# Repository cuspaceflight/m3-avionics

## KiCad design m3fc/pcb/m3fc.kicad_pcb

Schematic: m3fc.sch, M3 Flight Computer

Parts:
C1, C6: 10p; 0402; Farnell 2496790
C2: 4µ7; 0402; Farnell 2426952
C3, C4, C7, C8, C9, C14, C15, C16, C17: 100n; 0402; Farnell 2496771
C5: 1µ; 0402; Farnell 2496814
C10, C11: 2µ2; 0402; Farnell 2362088
C13: 10µ; 0603; Farnell 2456110
D1: RED; 0603-LED; Farnell 2314404
D2: YLW; 0603-LED; Farnell 2335804
D3: GRN; 0603-LED; Farnell 2290363
D4: D; SOD-323; Farnell 1459033
IC1: STM32F405RxTx; LQFP-64; Farnell 2064363
IC2: MS5611-01BA03; MS5611; Farnell 2362662
IC3: MCP2562; DFN-8-EP-MICROCHIP; Farnell 2448755
IC4: ADXL345; ADXL3x5; Farnell 1853935
J1: WEST TOP; TFML-110-02-L-D
J2: WEST BOT; SFML-110-02-L-D-LC
J3: EAST TOP; TFML-110-02-L-D
J4: EAST BOT; SFML-110-02-L-D-LC
LS1: SOUNDER; KSSG13J12-N; Farnell 2215089
P1: SWD_TC; TC2030-NL
Q1: NFET; SOT-23; Farnell 2069541
R1, R2, R3, R4, R5: 100; 0402; Farnell 9239111
Y1: 26M; XTAL-20x16; Farnell 2506952

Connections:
3v3: C2.2, C3.2, C4.2, C5.2, C7.2, C8.2, C9.2, C13.1, C14.1, C16.1, C17.1, D4.1, IC1.1 (VBAT), IC1.13 (VDDA), IC1.19 (VDD), IC1.32 (VDD), IC1.48 (VDD), IC1.64 (VDD), IC2.1 (VDD), IC3.5 (VIO), IC4.1 (VDD_IO), IC4.6 (Vs), J1.7, J2.7, LS1.1, P1.1 (VDD)
/3v3_AUX1: J1.13, J2.13
/3v3_AUX2: J1.15, J2.15
/3v3_DL: J1.11, J2.11
/3v3_IMU: J1.3, J2.3
/3v3_PYRO: J1.9, J2.9
/3v3_RADIO: J1.5, J2.5
/5v_AUX1: J3.11, J4.11
/5v_AUX2: J3.13, J4.13
/5v_CAM: J3.15, J4.15
/5v_CAN: C15.1, IC3.3 (VDD), J1.14, J2.14
/5v_IMU: J3.9, J4.9
/5v_RADIO: J3.7, J4.7
/ACCEL_CS: IC1.45 (PA12), IC4.7 (CS)
/ACCEL_INT: IC1.44 (PA11), IC4.8 (INT1)
/ACCEL_SCLK: IC1.34 (PB13), IC4.14 (SCLK)
/ACCEL_SDI: IC1.36 (PB15), IC4.13 (SDI)
/ACCEL_SDO: IC1.35 (PB14), IC4.12 (SDO)
/BARO_CS: IC1.24 (PC4), IC2.5 (CSB)
/BARO_SCLK: IC1.21 (PA5), IC2.8 (SCLK)
/BARO_SDI: IC1.23 (PA7), IC2.7 (SDI)
/BARO_SDO: IC1.22 (PA6), IC2.6 (SDO)
/BEEPER: IC1.14 (PA0), R1.1
/CAN+: IC3.7 (CANH), J1.18, J2.18
/CAN-: IC3.6 (CANL), J1.16, J2.16
/CAN_RXD: IC1.61 (PB8), IC3.4 (RXD)
/CAN_TXD: IC1.62 (PB9), IC3.1 (TXD)
/CHARGE: J3.17, J3.18, J4.17, J4.18
/JTCK: IC1.49 (PA14), J1.6, J2.6, P1.4 (SWDCLK)
/JTDI: IC1.50 (PA15), J2.8
/JTDO: IC1.55 (PB3), J1.8
/JTDR: J1.10, J2.10
/JTMS: IC1.46 (PA13), J1.4, J2.4, P1.2 (SWDIO)
/LED_GRN: IC1.17 (PA3), R4.1
/LED_RED: IC1.15 (PA1), R2.1
/LED_YLW: IC1.16 (PA2), R3.1
/PWR: J3.16, J4.16
/PYRO1: J3.8, J4.8
/PYRO2: J3.10, J4.10
/PYRO3: J3.12, J4.12
/PYRO4: J3.14, J4.14
/PYRO_SI: J3.5, J3.6, J4.5, J4.6
/PYRO_SO: J3.3, J3.4, J4.3, J4.4
/RSVD1: J1.12, J2.12
/RSVD2: J1.17, J2.17
/~RST: IC1.7 (NRST), P1.3 (~RST)
GND: C1.1, C2.1, C3.1, C4.1, C5.1, C6.2, C7.1, C8.1, C9.1, C10.2, C11.2, C13.2, C14.2, C15.2, C16.2, C17.2, D1.1, D2.1, D3.1, IC1.12 (VSSA), IC1.18 (VSS), IC1.60 (BOOT0), IC1.63 (VSS), IC2.2 (PS), IC2.3 (GND), IC3.2 (VSS), IC3.8 (STBY), IC3.EP (VSS), IC4.2 (GND), IC4.4 (GND), IC4.5 (GND), J1.1, J1.2, J1.19, J1.20, J2.1, J2.2, J2.19, J2.20, J3.1, J3.2, J3.19, J3.20, J4.1, J4.2, J4.19, J4.20, P1.5 (GND), Q1.2 (S), Y1.2, Y1.4
unnamed: C1.2, IC1.5 (PH0), Y1.1
unnamed: C6.1, R5.1, Y1.3
unnamed: C10.1, IC1.47 (VCAP_2)
unnamed: C11.1, IC1.31 (VCAP_1)
unnamed: D1.2, R2.2
unnamed: D2.2, R3.2
unnamed: D3.2, R4.2
unnamed: D4.2, LS1.2, Q1.3 (D)
unnamed: IC1.6 (PH1), R5.2
unnamed: Q1.1 (G), R1.2

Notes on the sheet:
INTERCONNECTS
PB4 is JTRST, DO NOT CONNECT (Errata 2.1.4)

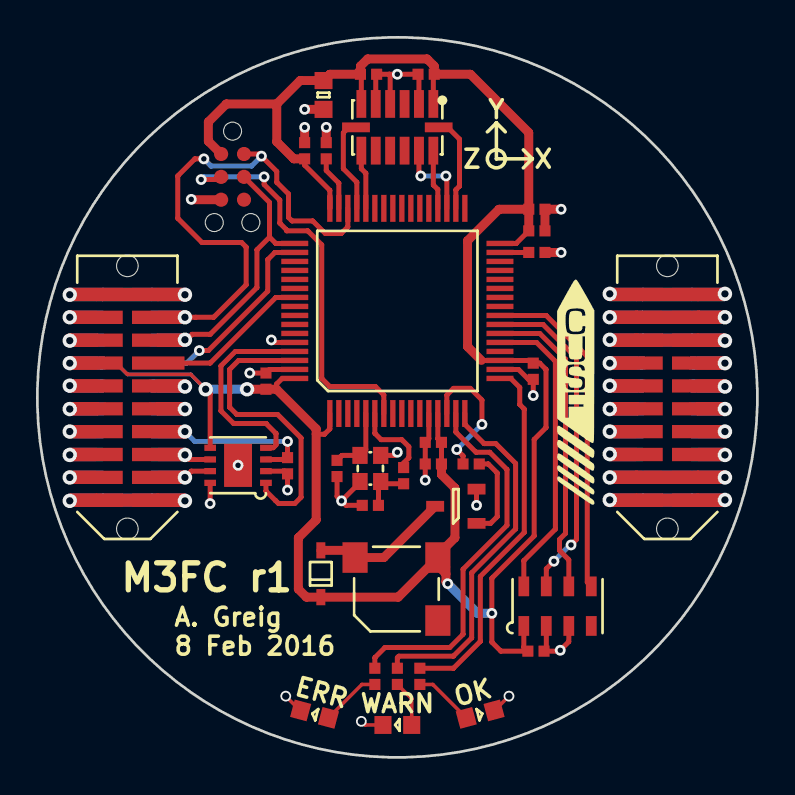
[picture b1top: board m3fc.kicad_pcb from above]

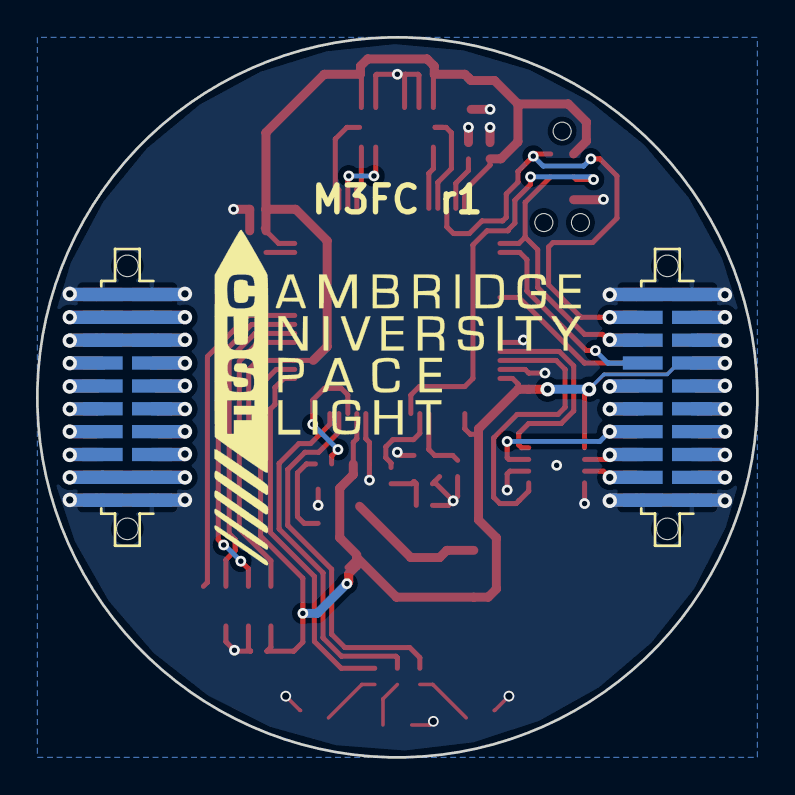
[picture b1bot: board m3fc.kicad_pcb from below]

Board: 2 copper layers, 40.0 x 40.0 mm, 37 parts (2 on the bottom side), 57 nets.

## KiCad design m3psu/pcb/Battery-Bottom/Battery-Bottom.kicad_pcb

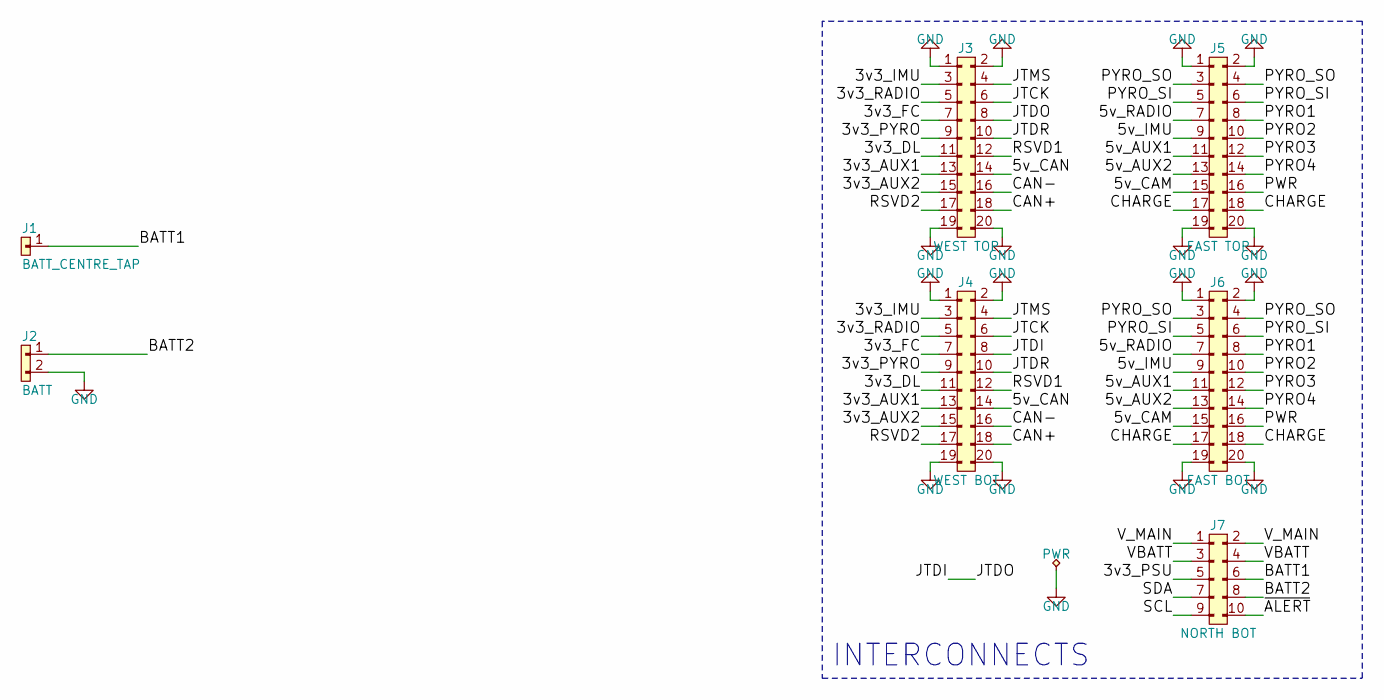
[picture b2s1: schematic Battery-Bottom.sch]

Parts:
J1: BATT_CENTRE_TAP; Socket_Strip_Straight_1x01
J2: BATT; Socket_Strip_Straight_1x02
J3: WEST TOP; TFML-110-02-L-D
J4: WEST BOT; SFML-110-02-L-D-LC
J5: EAST TOP; TFML-110-02-L-D
J6: EAST BOT; SFML-110-02-L-D-LC
J7: NORTH BOT; SFML-105-02-L-D-LC

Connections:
/3v3_AUX1: J3.13, J4.13
/3v3_AUX2: J3.15, J4.15
/3v3_DL: J3.11, J4.11
/3v3_FC: J3.7, J4.7
/3v3_IMU: J3.3, J4.3
/3v3_PSU: J7.5
/3v3_PYRO: J3.9, J4.9
/3v3_RADIO: J3.5, J4.5
/5v_AUX1: J5.11, J6.11
/5v_AUX2: J5.13, J6.13
/5v_CAM: J5.15, J6.15
/5v_CAN: J3.14, J4.14
/5v_IMU: J5.9, J6.9
/5v_RADIO: J5.7, J6.7
/BATT1: J1.1, J7.6
/BATT2: J2.1, J7.8
/CAN+: J3.18, J4.18
/CAN-: J3.16, J4.16
/CHARGE: J5.17, J5.18, J6.17, J6.18
/JTCK: J3.6, J4.6
/JTDI: J3.8, J4.8
/JTDR: J3.10, J4.10
/JTMS: J3.4, J4.4
/PWR: J5.16, J6.16
/PYRO1: J5.8, J6.8
/PYRO2: J5.10, J6.10
/PYRO3: J5.12, J6.12
/PYRO4: J5.14, J6.14
/PYRO_SI: J5.5, J5.6, J6.5, J6.6
/PYRO_SO: J5.3, J5.4, J6.3, J6.4
/RSVD1: J3.12, J4.12
/RSVD2: J3.17, J4.17
/SCL: J7.9
/SDA: J7.7
/VBATT: J7.3, J7.4
/V_MAIN: J7.1, J7.2
/~ALERT: J7.10
GND: J2.2, J3.1, J3.2, J3.19, J3.20, J4.1, J4.2, J4.19, J4.20, J5.1, J5.2, J5.19, J5.20, J6.1, J6.2, J6.19, J6.20

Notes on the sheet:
INTERCONNECTS

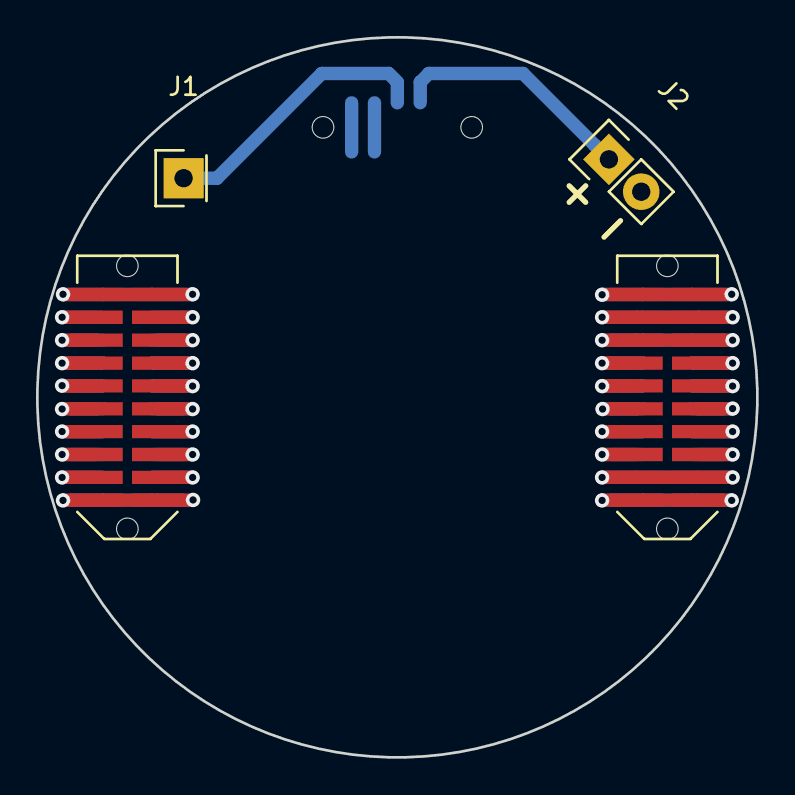
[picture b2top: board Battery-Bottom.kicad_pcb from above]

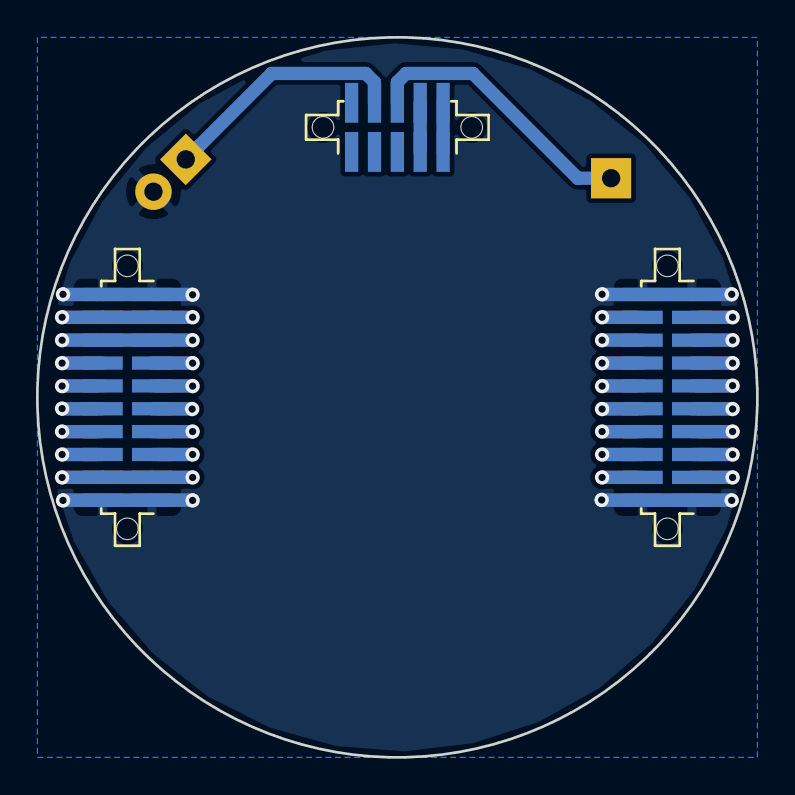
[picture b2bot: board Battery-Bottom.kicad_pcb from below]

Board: 2 copper layers, 40.0 x 40.0 mm, 7 parts (3 on the bottom side), 34 nets.

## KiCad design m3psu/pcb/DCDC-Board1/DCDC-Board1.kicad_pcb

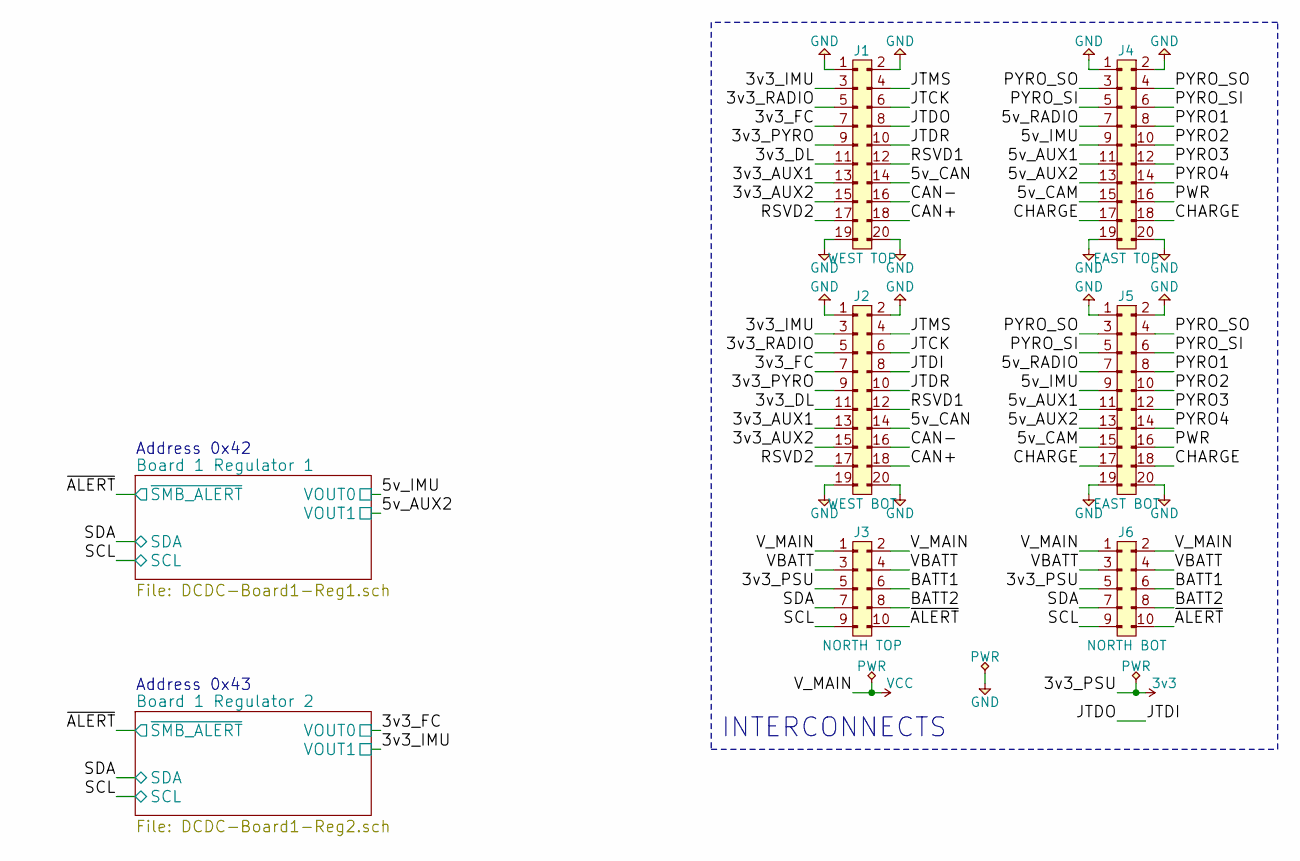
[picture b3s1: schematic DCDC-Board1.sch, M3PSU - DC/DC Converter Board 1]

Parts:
J1: WEST TOP; TFML-110-02-L-D
J2: WEST BOT; SFML-110-02-L-D-LC
J3: NORTH TOP; TFML-105-02-L-D
J4: EAST TOP; TFML-110-02-L-D
J5: EAST BOT; SFML-110-02-L-D-LC
J6: NORTH BOT; SFML-105-02-L-D-LC

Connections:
3v3: J3.5, J6.5
/3v3_AUX1: J1.13, J2.13
/3v3_AUX2: J1.15, J2.15
/3v3_DL: J1.11, J2.11
/3v3_FC: J1.7, J2.7; also elsewhere on the board
/3v3_IMU: J1.3, J2.3; also elsewhere on the board
/3v3_PYRO: J1.9, J2.9
/3v3_RADIO: J1.5, J2.5
/5v_AUX1: J4.11, J5.11
/5v_AUX2: J4.13, J5.13; also elsewhere on the board
/5v_CAM: J4.15, J5.15
/5v_CAN: J1.14, J2.14
/5v_IMU: J4.9, J5.9; also elsewhere on the board
/5v_RADIO: J4.7, J5.7
/BATT1: J3.6, J6.6
/BATT2: J3.8, J6.8
/CAN+: J1.18, J2.18
/CAN-: J1.16, J2.16
/CHARGE: J4.17, J4.18, J5.17, J5.18
/JTCK: J1.6, J2.6
/JTDI: J1.8, J2.8
/JTDR: J1.10, J2.10
/JTMS: J1.4, J2.4
/PWR: J4.16, J5.16
/PYRO1: J4.8, J5.8
/PYRO2: J4.10, J5.10
/PYRO3: J4.12, J5.12
/PYRO4: J4.14, J5.14
/PYRO_SI: J4.5, J4.6, J5.5, J5.6
/PYRO_SO: J4.3, J4.4, J5.3, J5.4
/RSVD1: J1.12, J2.12
/RSVD2: J1.17, J2.17
/SCL: J3.9, J6.9; also elsewhere on the board
/SDA: J3.7, J6.7; also elsewhere on the board
/VBATT: J3.3, J3.4, J6.3, J6.4
/~ALERT: J3.10, J6.10; also elsewhere on the board
GND: J1.1, J1.2, J1.19, J1.20, J2.1, J2.2, J2.19, J2.20, J4.1, J4.2, J4.19, J4.20, J5.1, J5.2, J5.19, J5.20; also elsewhere on the board
VCC: J3.1, J3.2, J6.1, J6.2; also elsewhere on the board

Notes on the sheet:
Address 0x42
Address 0x43
INTERCONNECTS

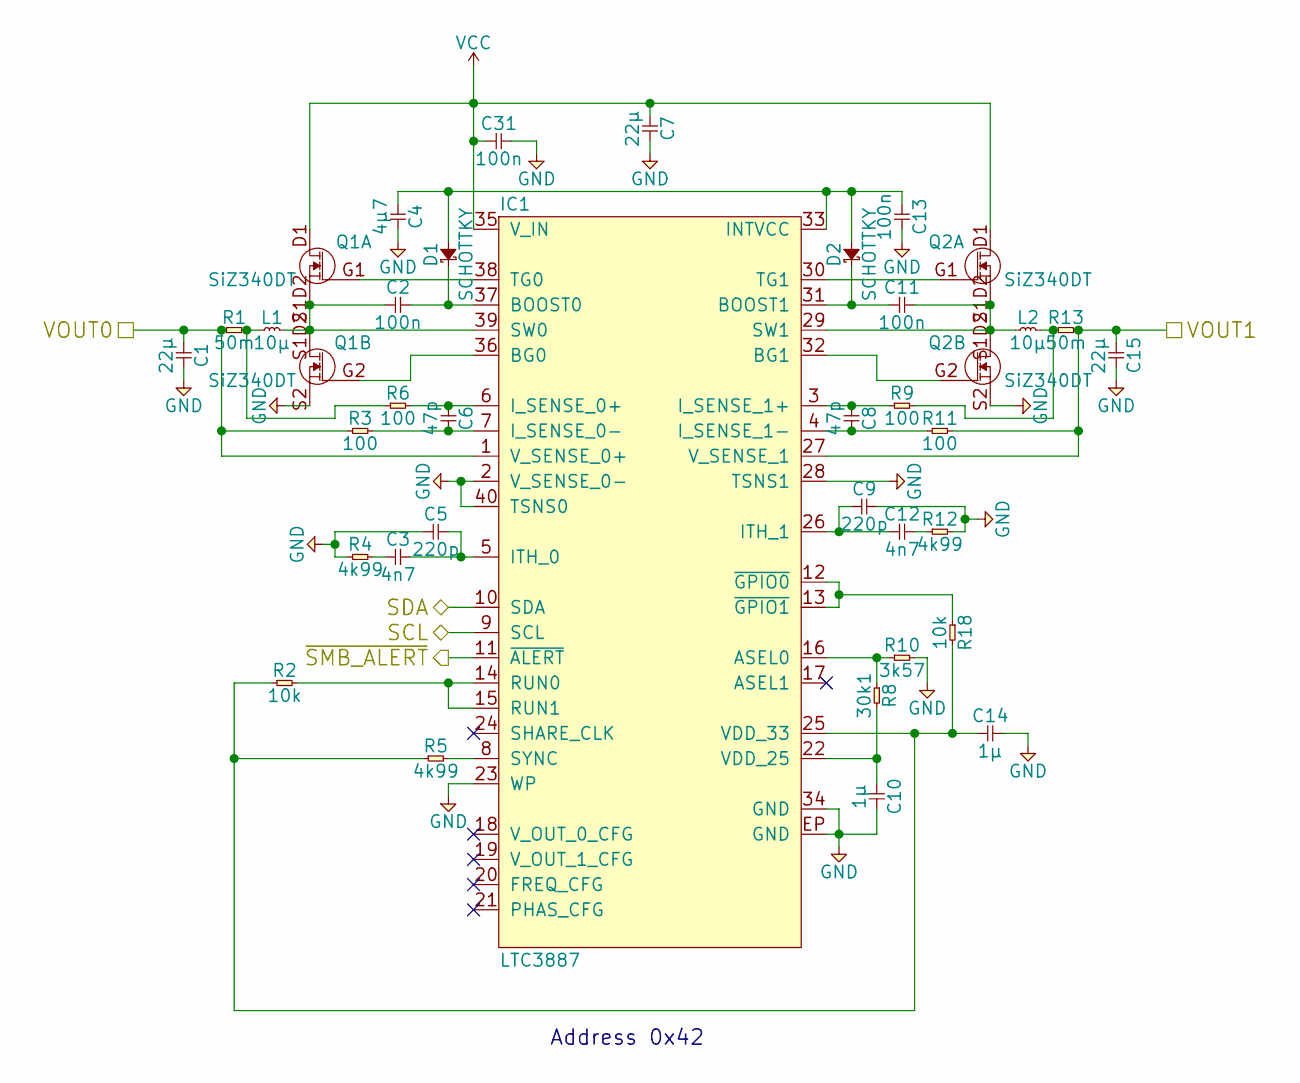
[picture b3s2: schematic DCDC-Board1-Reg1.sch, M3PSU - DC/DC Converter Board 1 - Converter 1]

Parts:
C1, C7, C15: 22µ; 0805; Farnell 2346925
C2, C11, C13, C31: 100n; 0402; Farnell 2496811
C3, C12: 4n7; 0402; Farnell 2496786
C4: 4µ7; 0402; Farnell 2346881
C5, C9: 220p; 0402; Farnell 2210772
C6, C8: 47p; 0402; Farnell 2210781
C10, C14: 1µ; 0402; Farnell 2218855
D1, D2: SCHOTTKY; 0603-LED; Farnell 2317558
IC1: LTC3887; QFN-40-EP-LTC-UJ; Farnell 2475658
L1, L2: 10µ; TYS5040; Farnell 2292532
Q1, Q2: SiZ340DT; PowerPair3x3; Farnell 2422226
R1, R13: 50m; 0603; Farnell 1506129
R2, R18: 10k; 0402; Farnell 2447096
R3, R6, R9, R11: 100; 0402; Farnell 2447095
R4, R5, R12: 4k99; 0402; Farnell 1469715
R8: 30k1; 0402; Farnell 2072900
R10: 3k57; 0402; Farnell 2302693

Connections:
/5v_AUX2: C15.1, IC1.27 (V_SENSE_1), R11.2, R13.2; also elsewhere on the board
/5v_IMU: C1.1, IC1.1 (V_SENSE_0+), R1.1, R3.1; also elsewhere on the board
/SCL: IC1.9 (SCL); also elsewhere on the board
/SDA: IC1.10 (SDA); also elsewhere on the board
/~ALERT: IC1.11 (~ALERT); also elsewhere on the board
GND: C1.2, C4.2, C5.1, C7.2, C9.2, C10.2, C13.2, C14.2, C15.2, C31.2, IC1.2 (V_SENSE_0-), IC1.23 (WP), IC1.28 (TSNS1), IC1.34 (GND), IC1.40 (TSNS0), IC1.EP (GND), Q1.S2, Q2.S2, R4.1, R10.2, R12.2; also elsewhere on the board
unnamed: C2.1, IC1.39 (SW0), L1.2, Q1.S1D2
unnamed: C2.2, D1.1, IC1.37 (BOOST0)
unnamed: C3.1, R4.2
unnamed: C3.2, C5.2, IC1.5 (ITH_0)
unnamed: C6.1, IC1.6 (I_SENSE_0+), R6.2
unnamed: C6.2, IC1.7 (I_SENSE_0-), R3.2
unnamed: C8.1, IC1.3 (I_SENSE_1+), R9.1
unnamed: C8.2, IC1.4 (I_SENSE_1-), R11.1
unnamed: C10.1, IC1.22 (VDD_25), R8.2
unnamed: C11.1, D2.1, IC1.31 (BOOST1)
unnamed: C11.2, IC1.29 (SW1), L2.1, Q2.S1D2
unnamed: C9.1, C12.1, IC1.26 (ITH_1)
unnamed: C12.2, R12.1
unnamed: C4.1, C13.1, D1.2, D2.2, IC1.33 (INTVCC)
unnamed: C14.1, IC1.25 (VDD_33), R2.1, R5.1, R18.2
unnamed: IC1.8 (SYNC), R5.2
unnamed: IC1.12 (~GPIO0), IC1.13 (~GPIO1), R18.1
unnamed: IC1.14 (RUN0), IC1.15 (RUN1), R2.2
unnamed: IC1.16 (ASEL0), R8.1, R10.1
unnamed: IC1.30 (TG1), Q2.G1
unnamed: IC1.32 (BG1), Q2.G2
unnamed: IC1.36 (BG0), Q1.G2
unnamed: IC1.38 (TG0), Q1.G1
unnamed: L1.1, R1.2, R6.1
unnamed: L2.2, R9.2, R13.1
VCC: C7.1, C31.1, IC1.35 (V_IN), Q1.D1 (S1D2), Q2.D1 (S1D2); also elsewhere on the board

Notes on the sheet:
Address 0x42

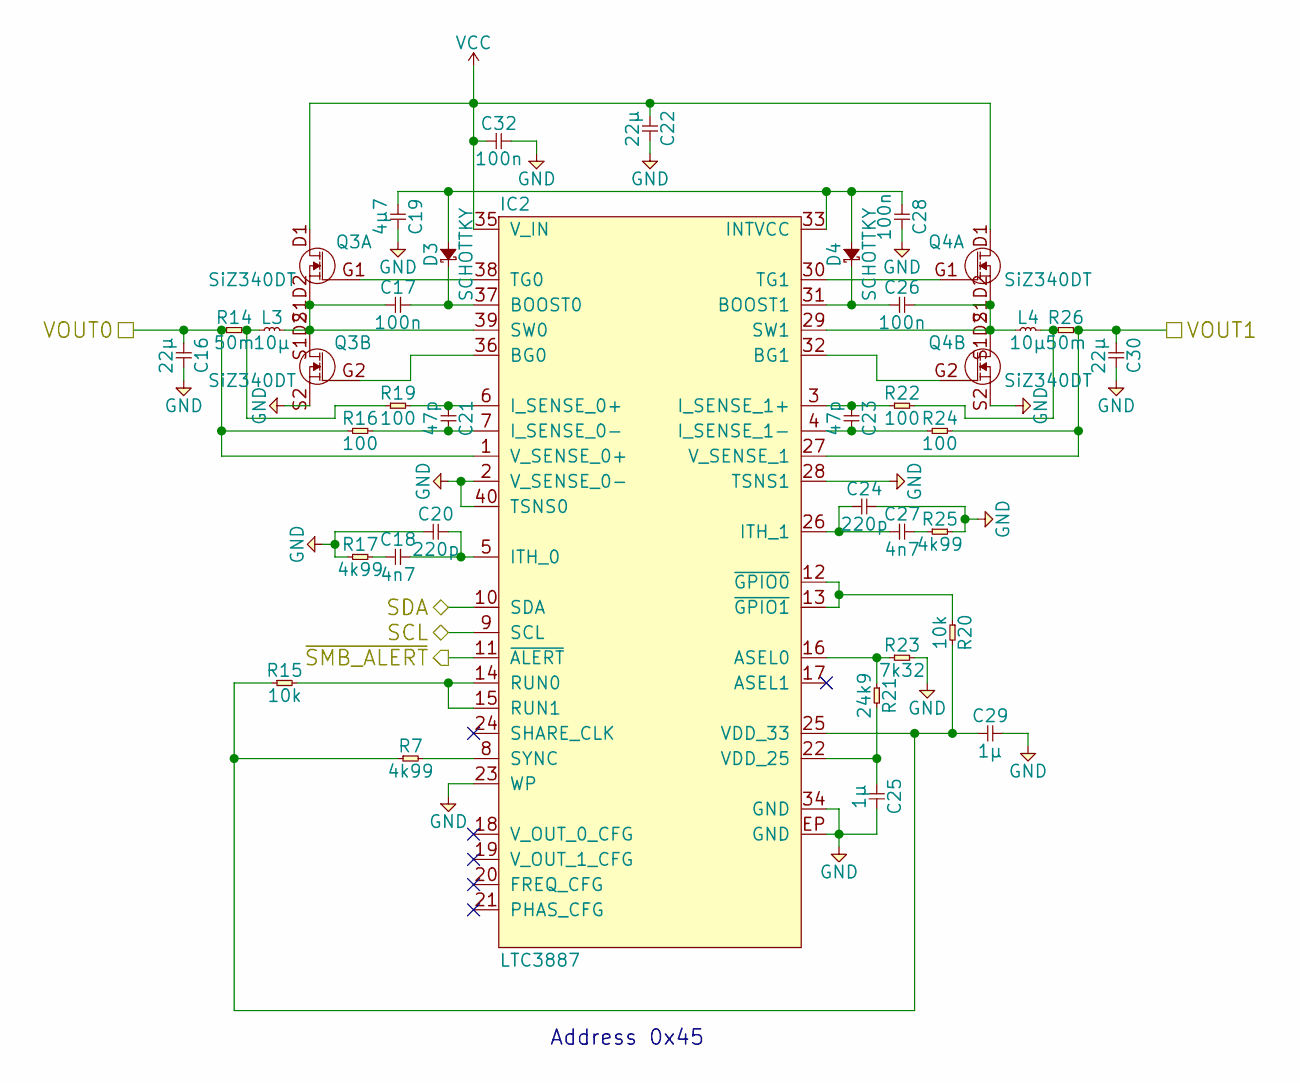
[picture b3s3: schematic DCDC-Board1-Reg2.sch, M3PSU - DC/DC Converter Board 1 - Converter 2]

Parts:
C16, C22, C30: 22µ; 0805; Farnell 2346925
C17, C26, C28, C32: 100n; 0402; Farnell 2496811
C18, C27: 4n7; 0402; Farnell 2496786
C19: 4µ7; 0402; Farnell 2346881
C20, C24: 220p; 0402; Farnell 2210772
C21, C23: 47p; 0402; Farnell 2210781
C25, C29: 1µ; 0402; Farnell 2218855
D3, D4: SCHOTTKY; 0603-LED; Farnell 2317558
IC2: LTC3887; QFN-40-EP-LTC-UJ; Farnell 2475658
L3, L4: 10µ; TYS5040; Farnell 2292532
Q3, Q4: SiZ340DT; PowerPair3x3; Farnell 2422226
R7, R17, R25: 4k99; 0402; Farnell 1469715
R14, R26: 50m; 0603; Farnell 1506129
R15, R20: 10k; 0402; Farnell 2447096
R16, R19, R22, R24: 100; 0402; Farnell 2447095
R21: 24k9; 0402; Farnell 1803690
R23: 7k32; 0402; Farnell 2073037

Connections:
/3v3_FC: C16.1, IC2.1 (V_SENSE_0+), R14.1, R16.1; also elsewhere on the board
/3v3_IMU: C30.1, IC2.27 (V_SENSE_1), R24.2, R26.2; also elsewhere on the board
/SCL: IC2.9 (SCL); also elsewhere on the board
/SDA: IC2.10 (SDA); also elsewhere on the board
/~ALERT: IC2.11 (~ALERT); also elsewhere on the board
GND: C16.2, C19.2, C20.1, C22.2, C24.2, C25.2, C28.2, C29.2, C30.2, C32.2, IC2.2 (V_SENSE_0-), IC2.23 (WP), IC2.28 (TSNS1), IC2.34 (GND), IC2.40 (TSNS0), IC2.EP (GND), Q3.S2, Q4.S2, R17.1, R23.2, R25.2; also elsewhere on the board
unnamed: C17.1, IC2.39 (SW0), L3.2, Q3.S1D2
unnamed: C17.2, D3.1, IC2.37 (BOOST0)
unnamed: C18.1, R17.2
unnamed: C18.2, C20.2, IC2.5 (ITH_0)
unnamed: C19.1, C28.1, D3.2, D4.2, IC2.33 (INTVCC)
unnamed: C21.1, IC2.6 (I_SENSE_0+), R19.2
unnamed: C21.2, IC2.7 (I_SENSE_0-), R16.2
unnamed: C23.1, IC2.3 (I_SENSE_1+), R22.1
unnamed: C23.2, IC2.4 (I_SENSE_1-), R24.1
unnamed: C24.1, C27.1, IC2.26 (ITH_1)
unnamed: C25.1, IC2.22 (VDD_25), R21.2
unnamed: C26.1, D4.1, IC2.31 (BOOST1)
unnamed: C26.2, IC2.29 (SW1), L4.1, Q4.S1D2
unnamed: C27.2, R25.1
unnamed: C29.1, IC2.25 (VDD_33), R7.1, R15.1, R20.2
unnamed: IC2.8 (SYNC), R7.2
unnamed: IC2.12 (~GPIO0), IC2.13 (~GPIO1), R20.1
unnamed: IC2.14 (RUN0), IC2.15 (RUN1), R15.2
unnamed: IC2.16 (ASEL0), R21.1, R23.1
unnamed: IC2.30 (TG1), Q4.G1
unnamed: IC2.32 (BG1), Q4.G2
unnamed: IC2.36 (BG0), Q3.G2
unnamed: IC2.38 (TG0), Q3.G1
unnamed: L3.1, R14.2, R19.1
unnamed: L4.2, R22.2, R26.1
VCC: C22.1, C32.1, IC2.35 (V_IN), Q3.D1 (S1D2), Q4.D1 (S1D2); also elsewhere on the board

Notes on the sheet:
Address 0x45

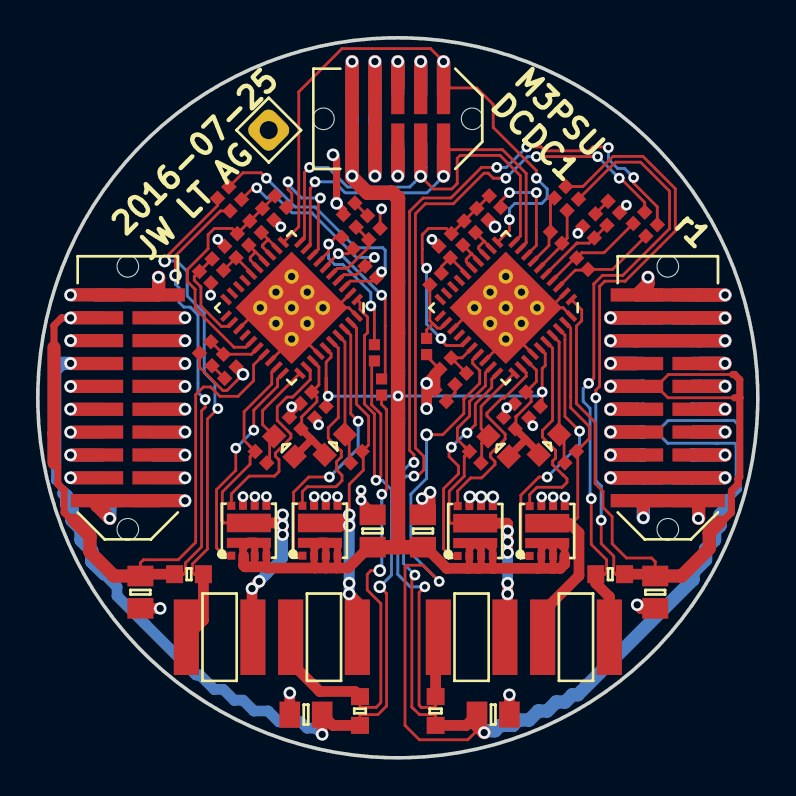
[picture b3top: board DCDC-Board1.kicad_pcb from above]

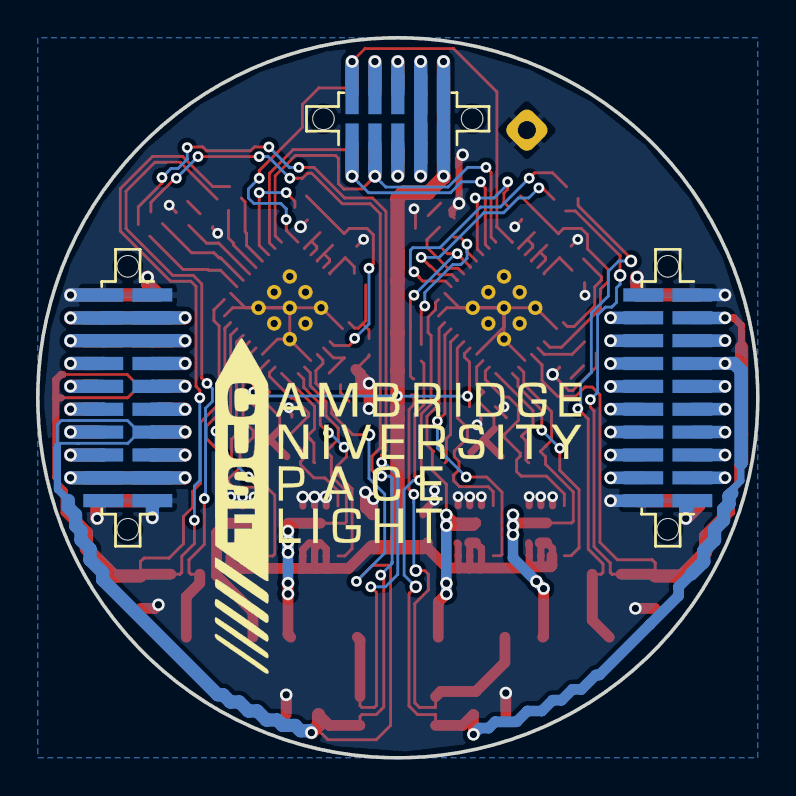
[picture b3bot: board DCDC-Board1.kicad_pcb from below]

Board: 2 copper layers, 40.0 x 40.0 mm, 78 parts (3 on the bottom side), 88 nets.

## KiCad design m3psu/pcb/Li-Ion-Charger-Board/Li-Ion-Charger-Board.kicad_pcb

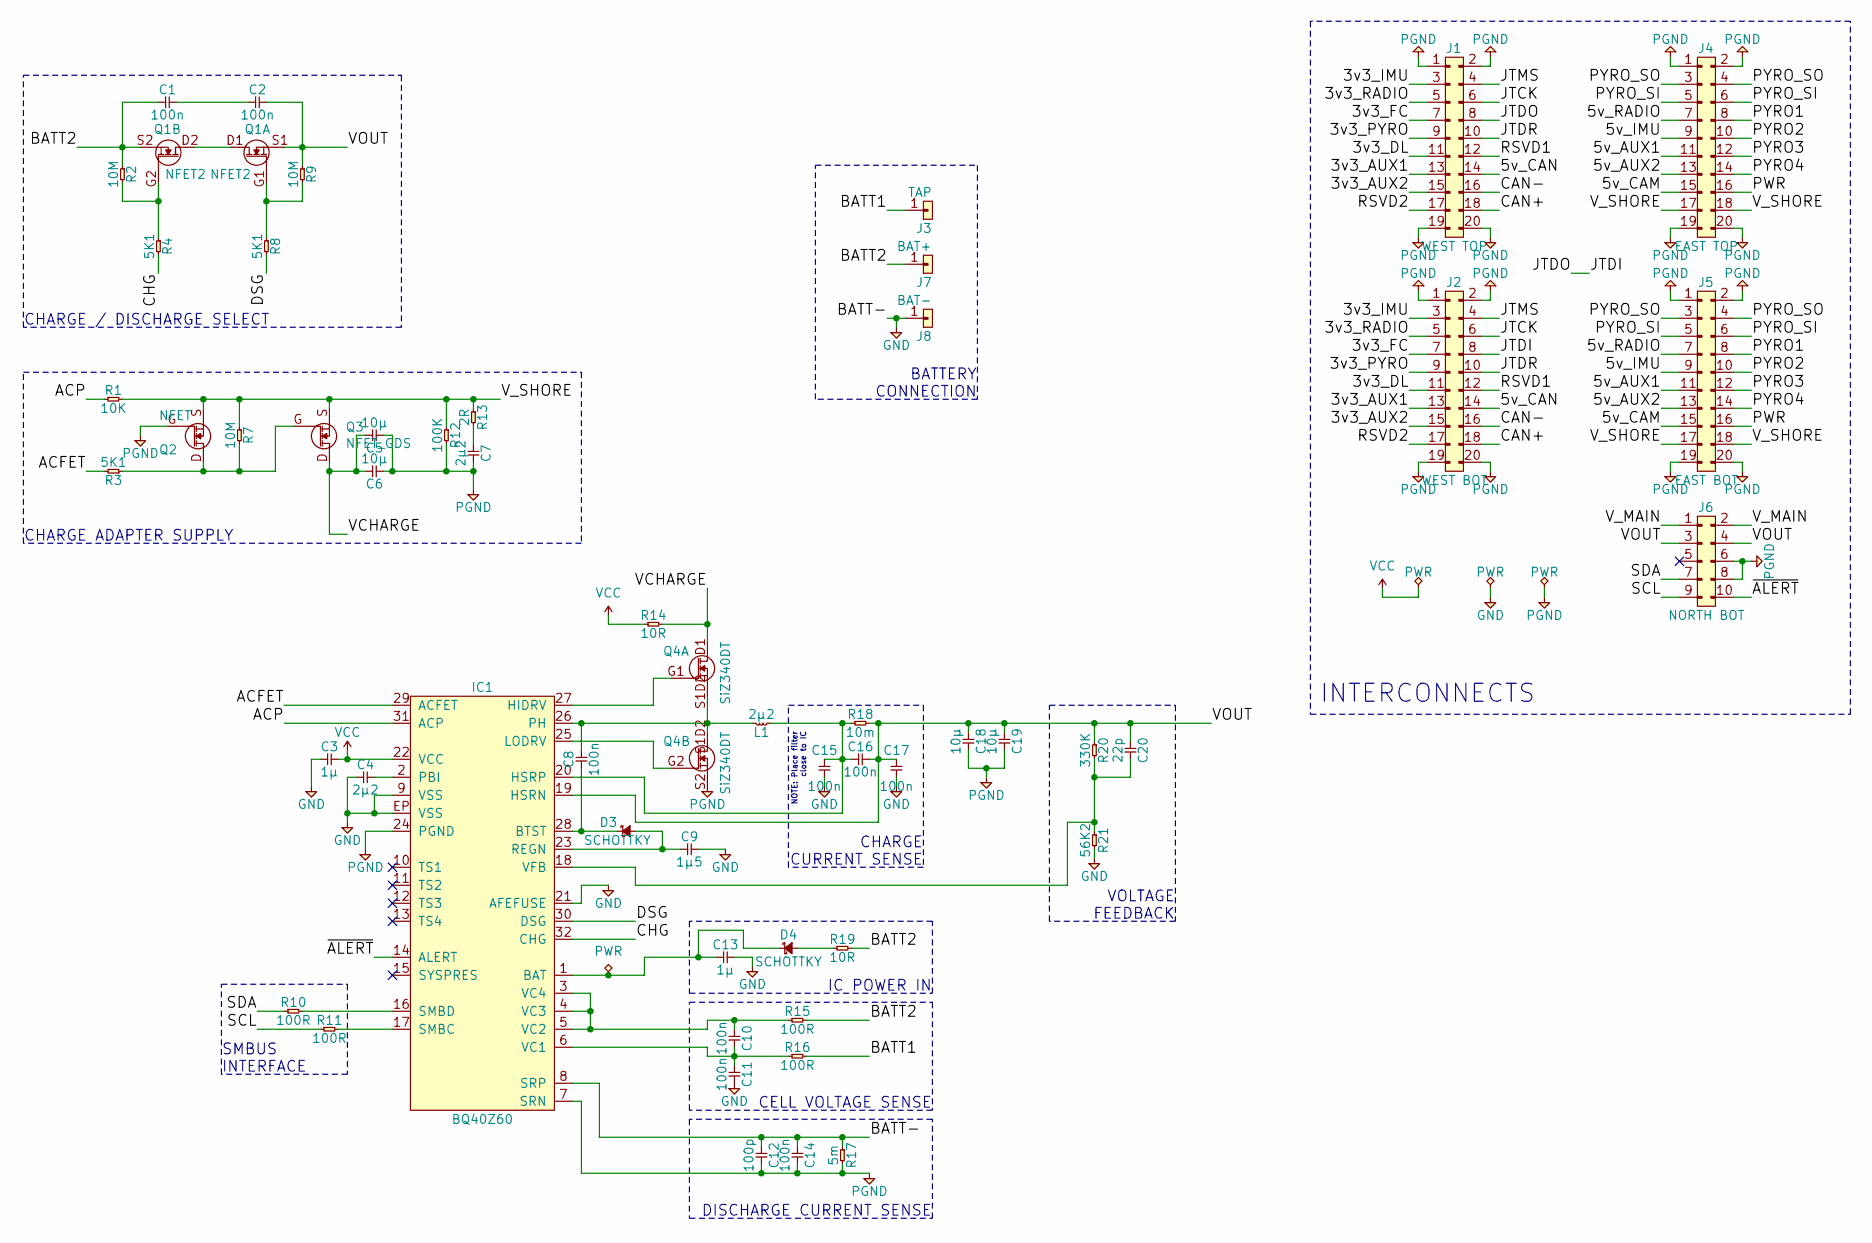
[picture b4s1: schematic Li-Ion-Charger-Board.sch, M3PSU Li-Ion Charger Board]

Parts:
C1, C2, C8, C10, C11, C14, C15, C16, C17: 100n; 0402; Farnell 2218856
C3, C13: 1µ; 0402; Farnell 2218855
C4, C7: 2µ2; 0805; Farnell 1657931
C5, C6, C18, C19: 10µ; 1210; Farnell 1845762
C9: 1µ5; 0603; Farnell 2211176
C12: 100p; 0402; Farnell 2496792
C20: 22p; 0402; Farnell 2496799
D3, D4: SCHOTTKY; SOD-323; Farnell 1459033
IC1: BQ40Z60; QFN-32-EP-TI; Farnell 2471154
J1: WEST TOP; TFML-110-02-L-D
J2: WEST BOT; SFML-110-02-L-D-LC
J3: TAP; SIL-254P-01
J4: EAST TOP; TFML-110-02-L-D
J5: EAST BOT; SFML-110-02-L-D-LC
J6: NORTH BOT; SFML-105-02-L-D-LC
J7: BAT+; SIL-254P-01
J8: BAT-; SIL-254P-01
L1: 2µ2; SRP5030T; Farnell 2309885
Q1: NFET2; PowerFLAT-5x6; Farnell 2098274
Q2: NFET; SOT-883-B; Farnell 2498598
Q3: NFET_GDS; SON2x2N; Farnell 2544998
Q4: SiZ340DT; PowerPair-3x3; Farnell 2422226
R1: 10K; 0402; Farnell 1469669
R2, R7, R9: 10M; 0402; Farnell 1469670
R3, R4, R8: 5K1; 0402; Farnell 1458805
R10, R11, R15, R16: 100R; 0402; Farnell 9239111
R12: 100K; 0402; Farnell 9239472
R13: 2R; 0402; Farnell 2059192
R14, R19: 10R; 0402; Farnell 1652742
R17: 5m; 0805; Farnell 2518218
R18: 10m; 0603; Farnell 2503038
R20: 330K; 0402; Farnell 2502450
R21: 56K2; 0402; Farnell 2059175

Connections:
/3v3_AUX1: J1.13, J2.13
/3v3_AUX2: J1.15, J2.15
/3v3_DL: J1.11, J2.11
/3v3_FC: J1.7, J2.7
/3v3_IMU: J1.3, J2.3
/3v3_PYRO: J1.9, J2.9
/3v3_RADIO: J1.5, J2.5
/5v_AUX1: J4.11, J5.11
/5v_AUX2: J4.13, J5.13
/5v_CAM: J4.15, J5.15
/5v_CAN: J1.14, J2.14
/5v_IMU: J4.9, J5.9
/5v_RADIO: J4.7, J5.7
/ACFET: IC1.29 (ACFET), R3.2
/ACP: IC1.31 (ACP), R1.1
/BATT1: J3.1, R16.2
/BATT2: C1.1, J7.1, Q1.S2 (S), R2.1, R15.2, R19.2
/CAN+: J1.18, J2.18
/CAN-: J1.16, J2.16
/CHG: IC1.32 (CHG), R4.2
/DSG: IC1.30 (DSG), R8.2
/JTCK: J1.6, J2.6
/JTDI: J1.8, J2.8
/JTDR: J1.10, J2.10
/JTMS: J1.4, J2.4
/PWR: J4.16, J5.16
/PYRO1: J4.8, J5.8
/PYRO2: J4.10, J5.10
/PYRO3: J4.12, J5.12
/PYRO4: J4.14, J5.14
/PYRO_SI: J4.5, J4.6, J5.5, J5.6
/PYRO_SO: J4.3, J4.4, J5.3, J5.4
/RSVD1: J1.12, J2.12
/RSVD2: J1.17, J2.17
/SCL: J6.9, R11.1
/SDA: J6.7, R10.1
/VCHARGE: C5.2, C6.2, Q3.D, Q4.D1 (S1D2), R14.2
/VOUT: C2.2, C16.2, C17.2, C18.1, C19.1, C20.1, IC1.19 (HSRN), J6.3, J6.4, Q1.S1 (S), R9.1, R18.2, R20.1
/V_MAIN: J6.1, J6.2
/V_SHORE: J4.17, J4.18, J5.17, J5.18, Q2.S, Q3.S, R1.2, R7.1, R12.1, R13.1
/~ALERT: IC1.14 (ALERT), J6.10
GND: C3.1, C4.1, C9.2, C11.2, C12.1, C13.2, C14.1, C15.1, C17.1, IC1.8 (SRP), IC1.9 (VSS), IC1.21 (AFEFUSE), IC1.EP (VSS), J8.1, R17.1, R21.2
unnamed: C1.2, C2.1
unnamed: C4.2, IC1.2 (PBI)
unnamed: C7.1, R13.2
unnamed: C8.1, D3.1, IC1.28 (BTST)
unnamed: C8.2, IC1.26 (PH), L1.2, Q4.S1D2
unnamed: C9.1, D3.2, IC1.23 (REGN)
unnamed: C10.1, IC1.3 (VC4), IC1.4 (VC3), IC1.5 (VC2), R15.1
unnamed: C10.2, C11.1, IC1.6 (VC1), R16.1
unnamed: C13.1, D4.1, IC1.1 (BAT)
unnamed: C15.2, C16.1, IC1.20 (HSRP), L1.1, R18.1
unnamed: C20.2, IC1.18 (VFB), R20.2, R21.1
unnamed: D4.2, R19.1
unnamed: IC1.16 (SMBD), R10.2
unnamed: IC1.17 (SMBC), R11.2
unnamed: IC1.25 (LODRV), Q4.G2
unnamed: IC1.27 (HIDRV), Q4.G1
unnamed: Q1.D1 (D), Q1.D2 (D)
unnamed: Q1.G1 (G), R8.1, R9.2
unnamed: Q1.G2 (G), R2.2, R4.1
unnamed: Q2.D, Q3.G, R3.1, R7.2
PGND: C5.1, C6.1, C7.2, C12.2, C14.2, C18.2, C19.2, IC1.7 (SRN), IC1.24 (PGND), J1.1, J1.2, J1.19, J1.20, J2.1, J2.2, J2.19, J2.20, J4.1, J4.2, J4.19, J4.20, J5.1, J5.2, J5.19, J5.20, J6.6, J6.8, Q2.G, Q4.S2, R12.2, R17.2
VCC: C3.2, IC1.22 (VCC), R14.1

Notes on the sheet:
INTERCONNECTS
NOTE: Place filter close to IC
SMBUS INTERFACE
DISCHARGE CURRENT SENSE
CHARGE / DISCHARGE SELECT
IC POWER IN
CELL VOLTAGE SENSE
VOLTAGE FEEDBACK
CHARGE ADAPTER SUPPLY
CHARGE CURRENT SENSE
BATTERY CONNECTION

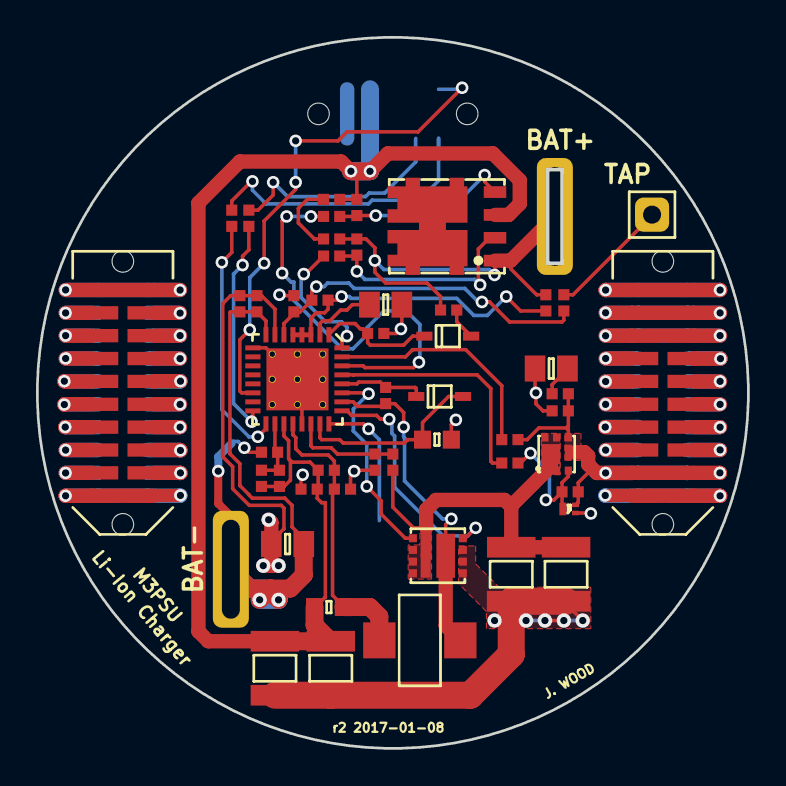
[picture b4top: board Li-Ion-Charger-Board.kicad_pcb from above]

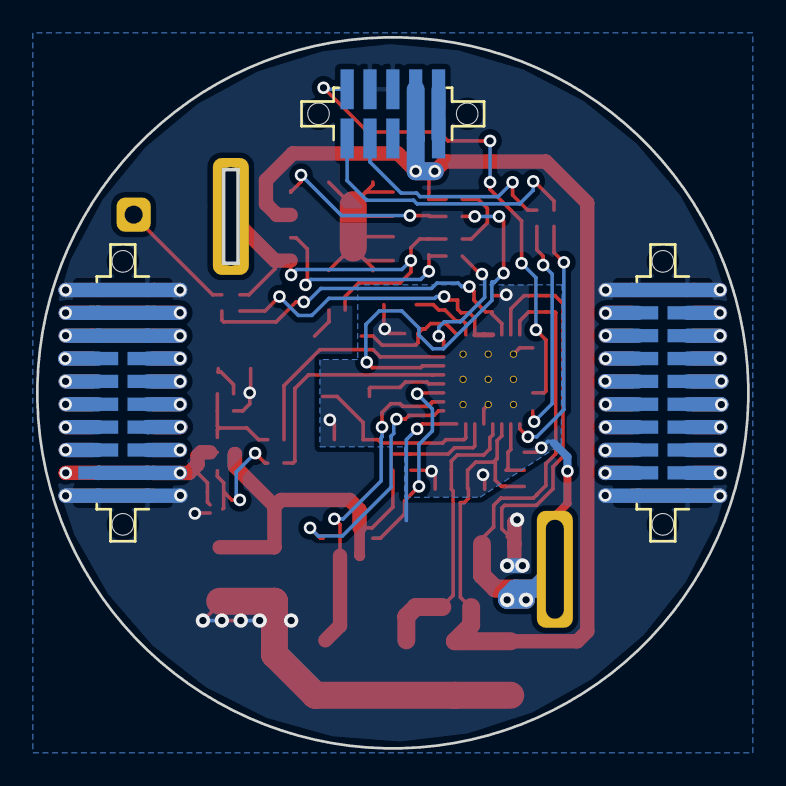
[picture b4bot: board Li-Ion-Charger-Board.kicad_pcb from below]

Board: 2 copper layers, 39.5 x 39.5 mm, 55 parts (3 on the bottom side), 64 nets.
